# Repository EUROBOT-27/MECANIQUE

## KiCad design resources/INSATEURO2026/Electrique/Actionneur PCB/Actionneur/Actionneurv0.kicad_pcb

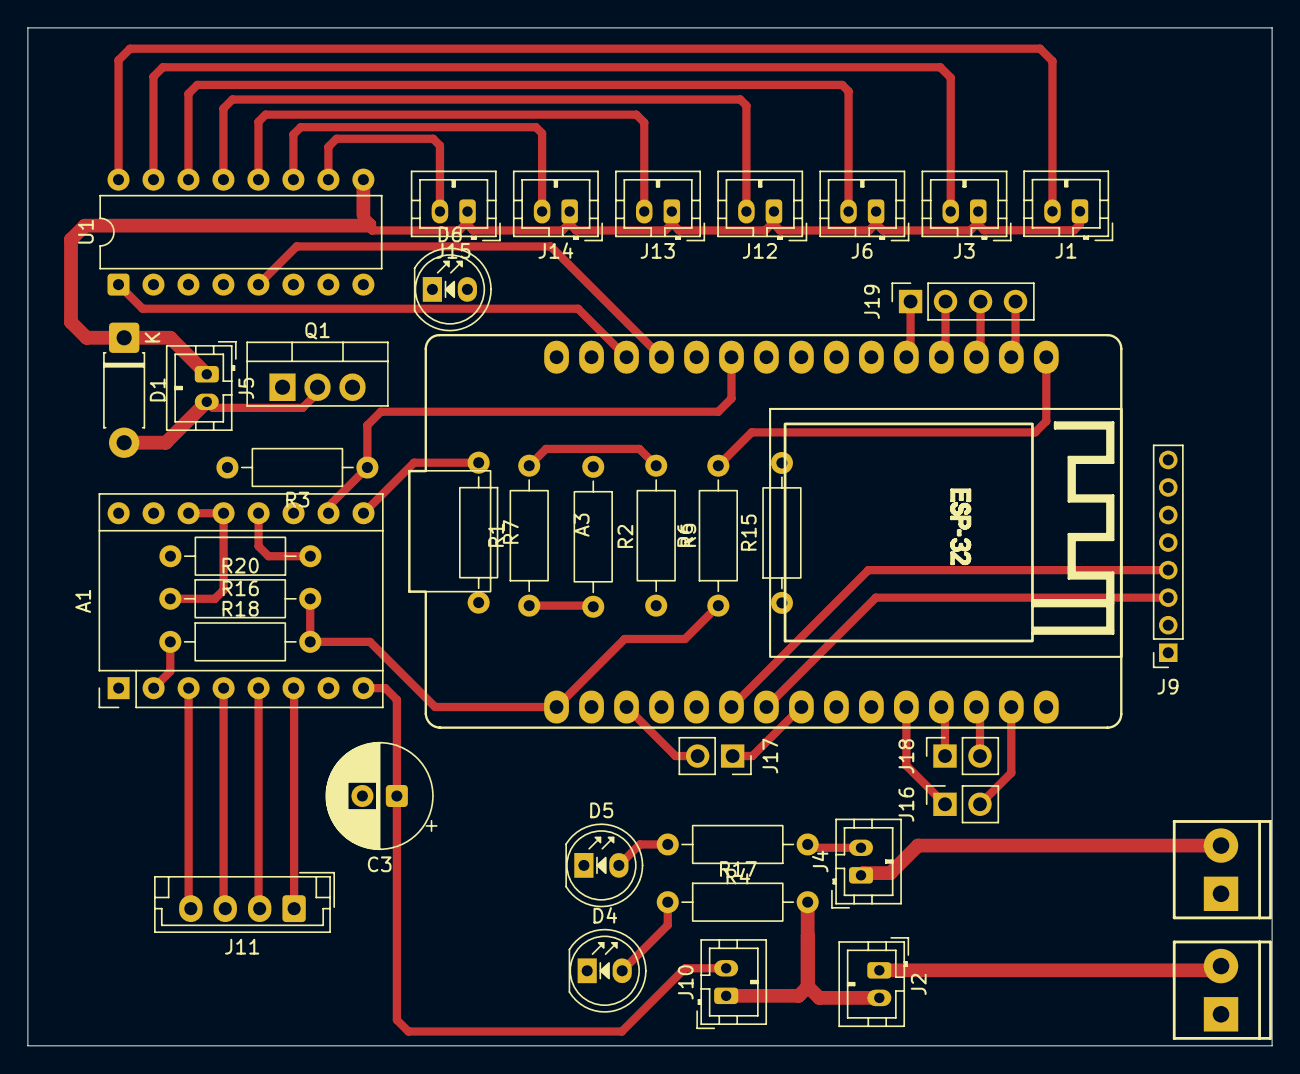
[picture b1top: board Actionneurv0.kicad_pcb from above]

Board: 2 copper layers, 90.3 x 73.9 mm, 40 parts (0 on the bottom side), 52 nets.

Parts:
A1: Pololu_Breakout_DRV8825; Pololu_Breakout-16_15.2x20.3mm
A3: ESP32_DevKit_V1_DOIT_30GPIOs; DOIT_ESP32_DEVKIT_30Pins
C3: 220u; CP_Radial_D7.5mm_P2.50mm
D1: 1N4001; D_DO-41_SOD81_P7.62mm_Horizontal
D4, D5, D6: LED; LED_D5.0mm
J1: V1; JST_PH_B2B-PH-K_1x02_P2.00mm_Vertical
J2: 12V Switch; JST_PH_B2B-PH-K_1x02_P2.00mm_Vertical
J3: V2; JST_PH_B2B-PH-K_1x02_P2.00mm_Vertical
J4: 5V Switch; JST_PH_B2B-PH-K_1x02_P2.00mm_Vertical
J5: Pump Output; JST_PH_B2B-PH-K_1x02_P2.00mm_Vertical
J6: V3; JST_PH_B2B-PH-K_1x02_P2.00mm_Vertical
J7: 12V input; ScrewTerminal_1x02_P3.5mm_Blue
J8: 5V input; ScrewTerminal_1x02_P3.5mm_Blue
J9: Maestro; PinSocket_1x08_P2.00mm_Vertical
J10: Stepper Switch; JST_PH_B2B-PH-K_1x02_P2.00mm_Vertical
J11: Stepper connector; JST_EH_B4B-EH-A_1x04_P2.50mm_Vertical
J12: V4; JST_PH_B2B-PH-K_1x02_P2.00mm_Vertical
J13: V5; JST_PH_B2B-PH-K_1x02_P2.00mm_Vertical
J14: V6; JST_PH_B2B-PH-K_1x02_P2.00mm_Vertical
J15: V7; JST_PH_B2B-PH-K_1x02_P2.00mm_Vertical
J16, J17, J18: V6; PinSocket_1x02_P2.54mm_Vertical
J19: PinSocket_1x04_P2.54mm_Vertical
Q1: IRF530N; TO-220-3_Vertical
R1: 220; R_Axial_DIN0207_L6.3mm_D2.5mm_P10.16mm_Horizontal
R2: 100k; R_Axial_DIN0207_L6.3mm_D2.5mm_P10.16mm_Horizontal
R3, R6, R7, R15, R16, R18, R20: 10k; R_Axial_DIN0207_L6.3mm_D2.5mm_P10.16mm_Horizontal
R4, R5, R17: R; R_Axial_DIN0207_L6.3mm_D2.5mm_P10.16mm_Horizontal
U1: ULN2003A; DIP-16_W7.62mm

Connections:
12V: D1.1 (K), J1.1, J2.2, J3.1, J5.1, J6.1, J10.1, J12.1, J13.1, J14.1, J15.1, R17.2, U1.9 (COM)
+3.3V: A3.1 (3.3V), R6.1, R18.2, R20.2
+5V: A3.30 (VIN), J4.2, J9.2, R4.1
D5: A3.8 (D5), J17.1
D15: A3.3 (D15/ADC2_CH3), J17.2
D34: A3.19 (ADC1_CH6/D34), J19.2
D35: A3.20 (ADC1_CH7/D35), J19.1
DIR: A1.16 (DIR), A3.10 (D19)
EV1: J1.2, U1.16 (O1)
EV2: J3.2, U1.15 (O2)
EV3: J6.2, U1.14 (O3)
EV4: J12.2, U1.13 (O4)
EV5: J13.2, U1.12 (O5)
EV6: J14.2, U1.11 (O6)
EV7: J15.2, U1.10 (O7)
GND: A1.1 (GND), A1.7 (GND), A3.2 (GND), A3.29 (GND), C3.2, D4.1 (K), D5.1 (K), D6.1 (K), J7.1, J8.1, J9.1, Q1.3 (S), R2.1, R3.2, R7.2, R15.2, R16.2, U1.8 (GND)
M0: A1.10 (M0), A3.25 (ADC2_CH7/D27), R3.1
M1: A1.11 (M1), A3.24 (DAC2/ADC2_CH9/D26), R15.1
M2: A1.12 (M2), A3.23 (DAC1/ADC2_CH8/D25), R16.1
unnamed: A1.4 (A1), J11.3
unnamed: A1.3 (A2), J11.4
unnamed: A1.5 (B1), J11.2
unnamed: A1.6 (B2), J11.1
unnamed: A1.8 (VMOT), C3.1, J10.2
unnamed: A1.9 (~EN), R7.1
unnamed: A1.2 (~FLT), R18.1
unnamed: A1.13 (~RST), A1.14 (~SLP), R20.1
unnamed: A3.16 (EN), R6.2
unnamed: D1.2 (A), J5.2, Q1.2 (D)
unnamed: D4.2 (A), R17.1
unnamed: D5.2 (A), R4.2
unnamed: D6.2 (A), R5.2
unnamed: J2.1, J7.2
unnamed: J4.1, J8.2
unnamed: Q1.1 (G), R1.1, R2.2
PUMP Signal: A3.15 (D23), R1.2, R5.1
RX: A3.6 (RX2/GPIO16), J9.4
RX0: A3.12 (RX0/GPIO3), J18.1
SCL: A3.14 (D22/SCL), J16.2
SDA: A3.11 (D21/SDA), J16.1
STEP: A1.15 (STEP), A3.9 (D18)
TX: A3.7 (TX2/GPIO17), J9.3
TX0: A3.13 (TX0/GPIO1), J18.2
VN: A3.18 (ADC1_CH3/VN), J19.3
VP: A3.17 (ADC1_CH0/VP), J19.4
Valve1: A3.28 (ADC2_CH4/D13), U1.1 (I1)
Valve2: A3.26 (ADC2_CH6/D14), U1.2 (I2)
Valve3: A3.22 (ADC1_CH4/D33), U1.3 (I3)
Valve4: A3.21 (ADC1_CH4/D32), U1.4 (I4)
Valve5: A3.27 (ADC2_CH5/D12), U1.5 (I5)
Valve6: A3.5 (D4/ADC2_CH0), U1.6 (I6)
Valve7: A3.4 (D2/ADC2_CH2), U1.7 (I7)

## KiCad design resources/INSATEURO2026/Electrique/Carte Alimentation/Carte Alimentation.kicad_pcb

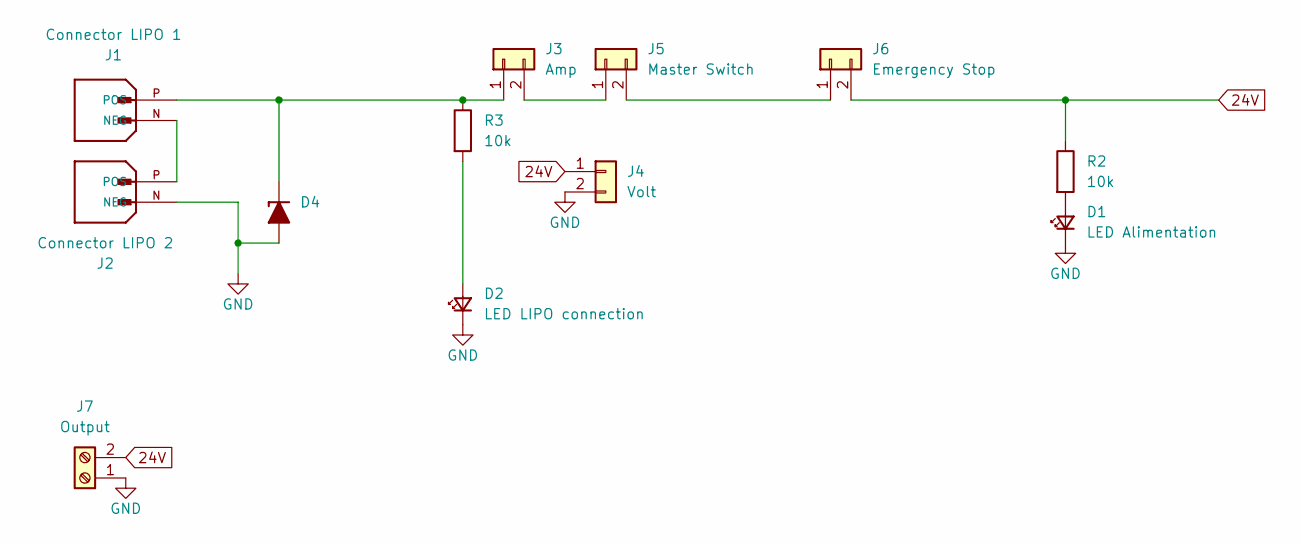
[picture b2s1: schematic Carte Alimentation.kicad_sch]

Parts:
D1: LED Alimentation; LED_D3.0mm
D2: LED LIPO connection; LED_D3.0mm
D4: P6KE24A; D_DO-15_P10.16mm_Horizontal_Zener
J1: Connector LIPO 1; AMASS_XT60-M; PARTREV V1.2
J2: Connector LIPO 2; AMASS_XT60-M; PARTREV V1.2
J3: Amp; JST_PH_B2B-PH-K_1x02_P2.00mm_Vertical
J4: Volt; JST_PH_B2B-PH-K_1x02_P2.00mm_Vertical; Part Number 1-0201FBV0T
J5: Master Switch; JST_PH_B2B-PH-K_1x02_P2.00mm_Vertical; Part Number 1-0201FBV0T
J6: Emergency Stop; JST_PH_B2B-PH-K_1x02_P2.00mm_Vertical; Part Number 1-0201FBV0T
J7: Output; TerminalBlock_Altech_AK300-2_P5.00mm
R2, R3: 10k; R_Axial_DIN0207_L6.3mm_D2.5mm_P10.16mm_Horizontal

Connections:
24V: J4.1, J6.2, J7.2, R2.1
GND: D1.1 (K), D2.1 (K), D4.2 (A), J2.N (NEG), J4.2, J7.1
unnamed: D1.2 (A), R2.2
unnamed: D2.2 (A), R3.2
unnamed: D4.1 (K), J1.P (POS), J3.1, R3.1
unnamed: J1.N (NEG), J2.P (POS)
unnamed: J3.2, J5.1
unnamed: J5.2, J6.1

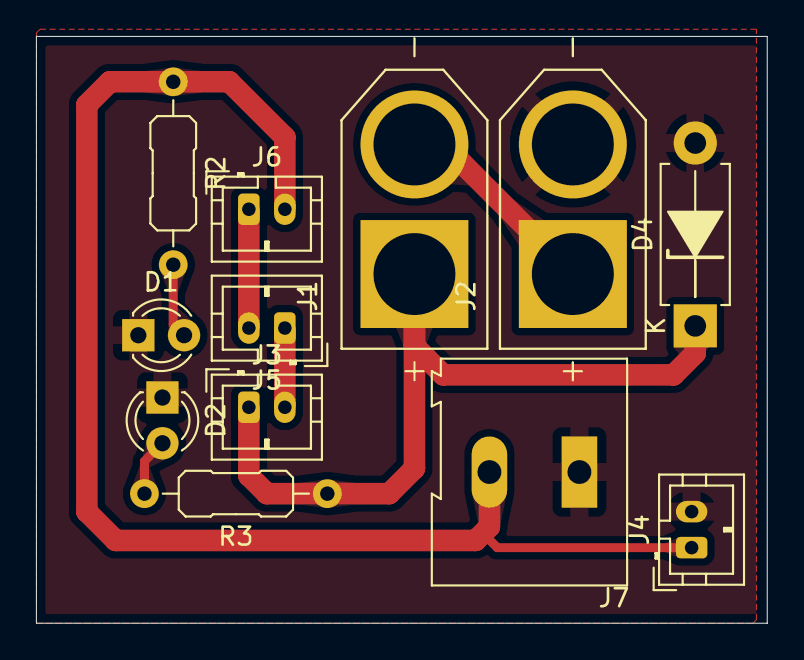
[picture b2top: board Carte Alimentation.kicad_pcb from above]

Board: 2 copper layers, 40.6 x 32.6 mm, 12 parts (0 on the bottom side), 8 nets.

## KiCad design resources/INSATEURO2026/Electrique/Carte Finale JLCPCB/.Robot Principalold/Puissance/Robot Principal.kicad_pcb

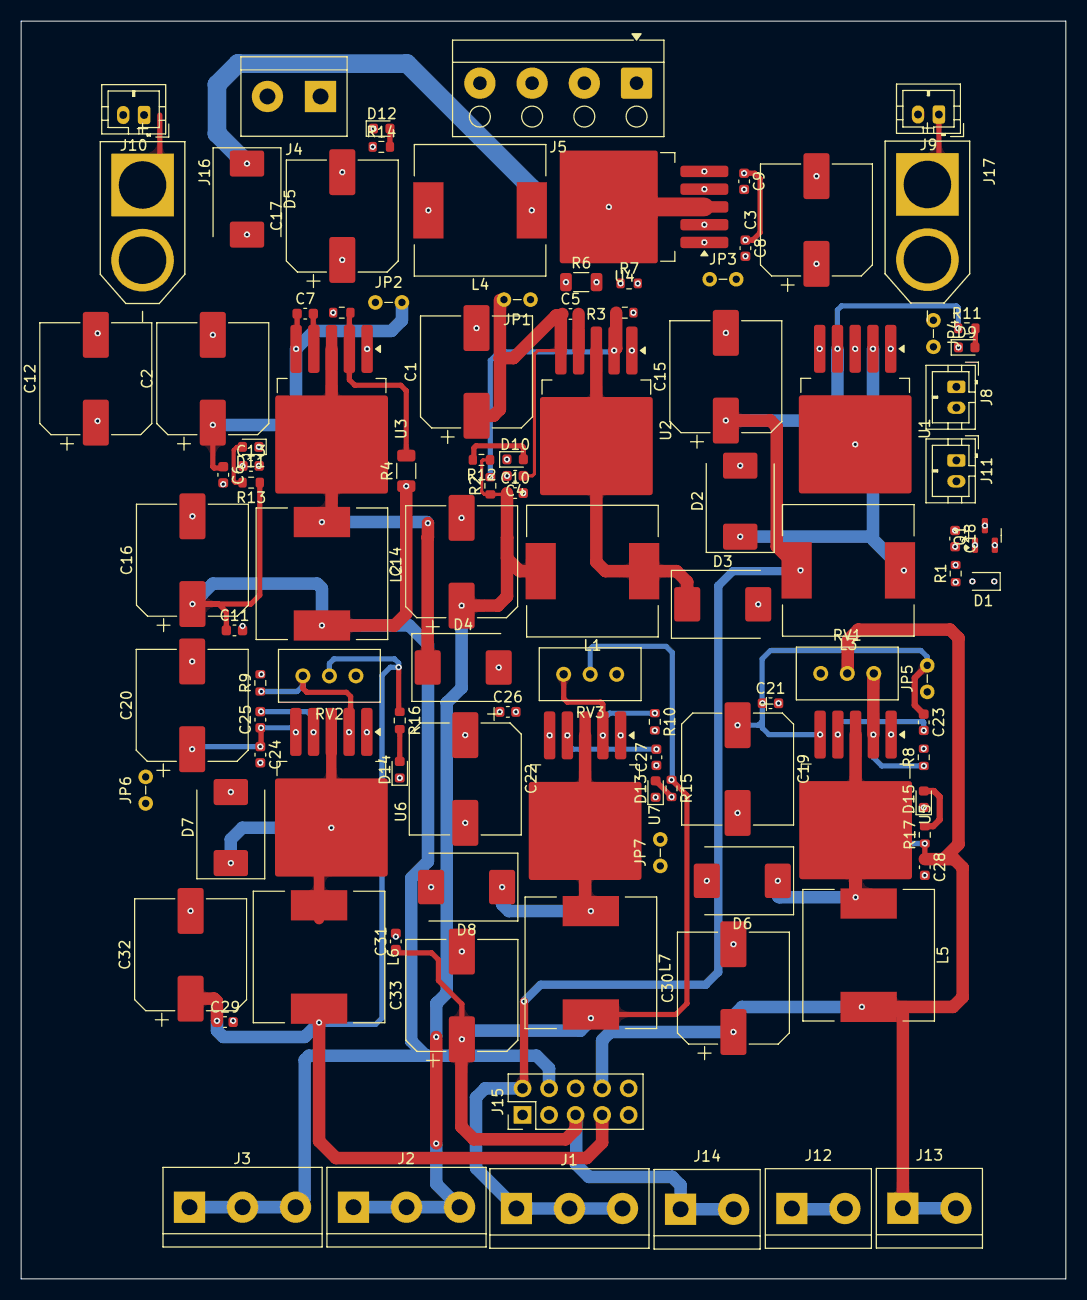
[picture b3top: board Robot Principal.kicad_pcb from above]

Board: 4 copper layers, 100.0 x 120.4 mm, 105 parts (0 on the bottom side), 47 nets.

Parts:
C1, C2, C3, C19, C20, C22: 220u; CP_Elec_10x10.5
C4, C5, C6, C7, C8, C9, C10, C11, C13, C21, C23, C24, C25, C26, C27, C28, C29, C31: 105; C_0603_1608Metric
C12: 1000u; CP_Elec_10x10.5
C14, C16, C17, C30, C32, C33: 330u; CP_Elec_10x10.5
C15: 560u; CP_Elec_10x10.5
C18: 100n; C_0603_1608Metric
D1: BZV55B10; D_SOD-323
D2: 1N5822; D_SMC
D3, D4, D5, D6, D7, D8: B540C; D_SMC
D9, D10, D11, D12, D13, D14, D15: LED; LED_0603_1608Metric
J1: 3.3v; TerminalBlock_bornier-3_P5.08mm
J2: 5V; TerminalBlock_bornier-3_P5.08mm
J3: 12V; TerminalBlock_bornier-3_P5.08mm
J4: 24V Out; TerminalBlock_bornier-2_P5.08mm
J5: Screw_Terminal_01x04; Altech_AK100_1x04_P5.00mm
J8: Emergency Stop; JST_PH_B2B-PH-K_1x02_P2.00mm_Vertical
J9: LIPO 1 VOLT; JST_PH_B2B-PH-K_1x02_P2.00mm_Vertical
J10: LIPO 2 VOLT; JST_PH_B2B-PH-K_1x02_P2.00mm_Vertical
J11: Master Switch; JST_PH_B2B-PH-K_1x02_P2.00mm_Vertical
J12, J13, J14: ADJ out; TerminalBlock_bornier-2_P5.08mm
J15: Conn_02x05_Top_Bottom; PinHeader_2x05_P2.54mm_Vertical
J16, J17: XT60-M; AMASS_XT60-M
JP1, JP2, JP3, JP4, JP5, JP6, JP7: Jumper_2_Small_Bridged; Jumper_P2.54mm_D0.7mm
L1, L2, L4, L5, L6, L7: 47uH; L_12x12mm_H6mm
L3: 33uH; L_12x12mm_H6mm
Q1: AO3401A; SOT-23
R1, R2: 10K; R_0603_1608Metric
R3, R7, R8, R9, R10: 3.3K; R_0603_1608Metric
R4: 13K; R_1206_3216Metric
R5: 1.5K; R_0603_1608Metric
R6: 60.4K; R_1206_3216Metric
R11, R12, R13, R14, R15, R16, R17: 1K; R_0603_1608Metric
RV1, RV2, RV3: R_Potentiometer; Potentiometer_Bourns_3296W_Vertical
U1: LM2596T-3.3; TO-263-5_TabPin3
U2, U3, U4, U5, U6, U7: XL4015; TO-263-5_TabPin3

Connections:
5V: C10.1, C14.1, J2.1, J2.2, J2.3, J15.3, L1.2, R2.1, R12.1
12V: C11.1, C16.1, J3.1, J3.2, J3.3, J15.4, L2.2, R4.1, R13.1
24V: C13.1, C17.1, J4.1, J4.2, L4.2, R6.1, R14.1
+3.3V: C15.1, J1.1, J1.2, J1.3, J15.2, L3.2, R11.1, U1.4 (FB)
ADJ1: C29.1, C32.1, J12.1, J12.2, J15.7, L6.2, R16.1, RV2.2
ADJ2: C28.1, C30.1, J13.1, J13.2, J15.8, L5.2, R17.1, RV1.2
GND: C1.2, C2.2, C3.2, C4.2, C6.2, C8.2, C10.2, C11.2, C12.2, C13.2, C14.2, C15.2, C16.2, C17.2, C18.2, C19.2, C20.2, C21.2, C22.2, C24.2, C26.2, C28.2, C29.2, C30.2, C31.2, C32.2, C33.2, D2.2 (A), D3.2 (A), D4.2 (A), D5.2 (A), D6.2 (A), D7.2 (A), D8.2 (A), D9.1 (K), D10.1 (K), D11.1 (K), D12.1 (K), D13.1 (K), D14.1 (K), D15.1 (K), J5.1, J5.2, J5.3, J5.4, J9.2, J10.2, J15.1, J15.6, J16.N (NEG), R1.2, R3.2, R5.2, R7.2, R8.2, R9.2, R10.2, RV1.3, RV2.3, RV3.3, U1.3 (GND), U1.5 (~ON/OFF), U2.1 (GND), U3.1 (GND), U4.1 (GND), U5.1 (GND), U6.1 (GND), U7.1 (GND)
unnamed: D1.2 (A), Q1.1 (G), R1.1
unnamed: D2.1 (K), L3.1, U1.2 (OUT)
unnamed: D3.1 (K), L1.1, U2.3 (SW)
unnamed: D4.1 (K), L2.1, U3.3 (SW)
unnamed: D5.1 (K), L4.1, U4.3 (SW)
unnamed: D6.1 (K), L5.1, U5.3 (SW)
unnamed: D7.1 (K), L6.1, U6.3 (SW)
unnamed: D8.1 (K), L7.1, U7.3 (SW)
unnamed: D9.2 (A), R11.2
unnamed: D10.2 (A), R12.2
unnamed: D11.2 (A), R13.2
unnamed: D12.2 (A), R14.2
unnamed: D13.2 (A), R15.2
unnamed: D14.2 (A), R16.2
unnamed: D15.2 (A), R17.2
unnamed: J10.1, J16.P (POS), J17.N (NEG)
unnamed: J8.2, J11.1
unnamed: J8.1, J9.1, J17.P (POS)
unnamed: C1.1, C4.1, C5.1, JP1.2 (B), U2.5 (VIN)
unnamed: C2.1, C6.1, C7.1, JP2.2 (B), U3.5 (VIN)
unnamed: C3.1, C8.1, C9.1, JP3.2 (B), U4.5 (VIN)
unnamed: JP4.2 (B), U1.1 (VIN)
unnamed: C19.1, C21.1, C23.1, JP5.2 (B), U5.5 (VIN)
unnamed: C20.1, C24.1, C25.1, JP6.2 (B), U6.5 (VIN)
unnamed: C22.1, C26.1, C27.1, JP7.2 (B), U7.5 (VIN)
unnamed: R2.2, R3.1, U2.2 (FB)
unnamed: C5.2, U2.4 (VC)
unnamed: R4.2, R5.1, U3.2 (FB)
unnamed: C7.2, U3.4 (VC)
unnamed: R6.2, R7.1, U4.2 (FB)
unnamed: C9.2, U4.4 (VC)
unnamed: R8.1, RV1.1, U5.2 (FB)
unnamed: C23.2, U5.4 (VC)
unnamed: R9.1, RV2.1, U6.2 (FB)
unnamed: C25.2, U6.4 (VC)
unnamed: R10.1, RV3.1, U7.2 (FB)
unnamed: C27.2, U7.4 (VC)
SERVO: C31.1, C33.1, J14.1, J14.2, J15.5, L7.2, R15.1, RV3.2
SUPPLY: J11.2, Q1.3 (D)
VDC: C12.1, C18.1, D1.1 (K), JP1.1 (A), JP2.1 (A), JP3.1 (A), JP4.1 (A), JP5.1 (A), JP6.1 (A), JP7.1 (A), Q1.2 (S)

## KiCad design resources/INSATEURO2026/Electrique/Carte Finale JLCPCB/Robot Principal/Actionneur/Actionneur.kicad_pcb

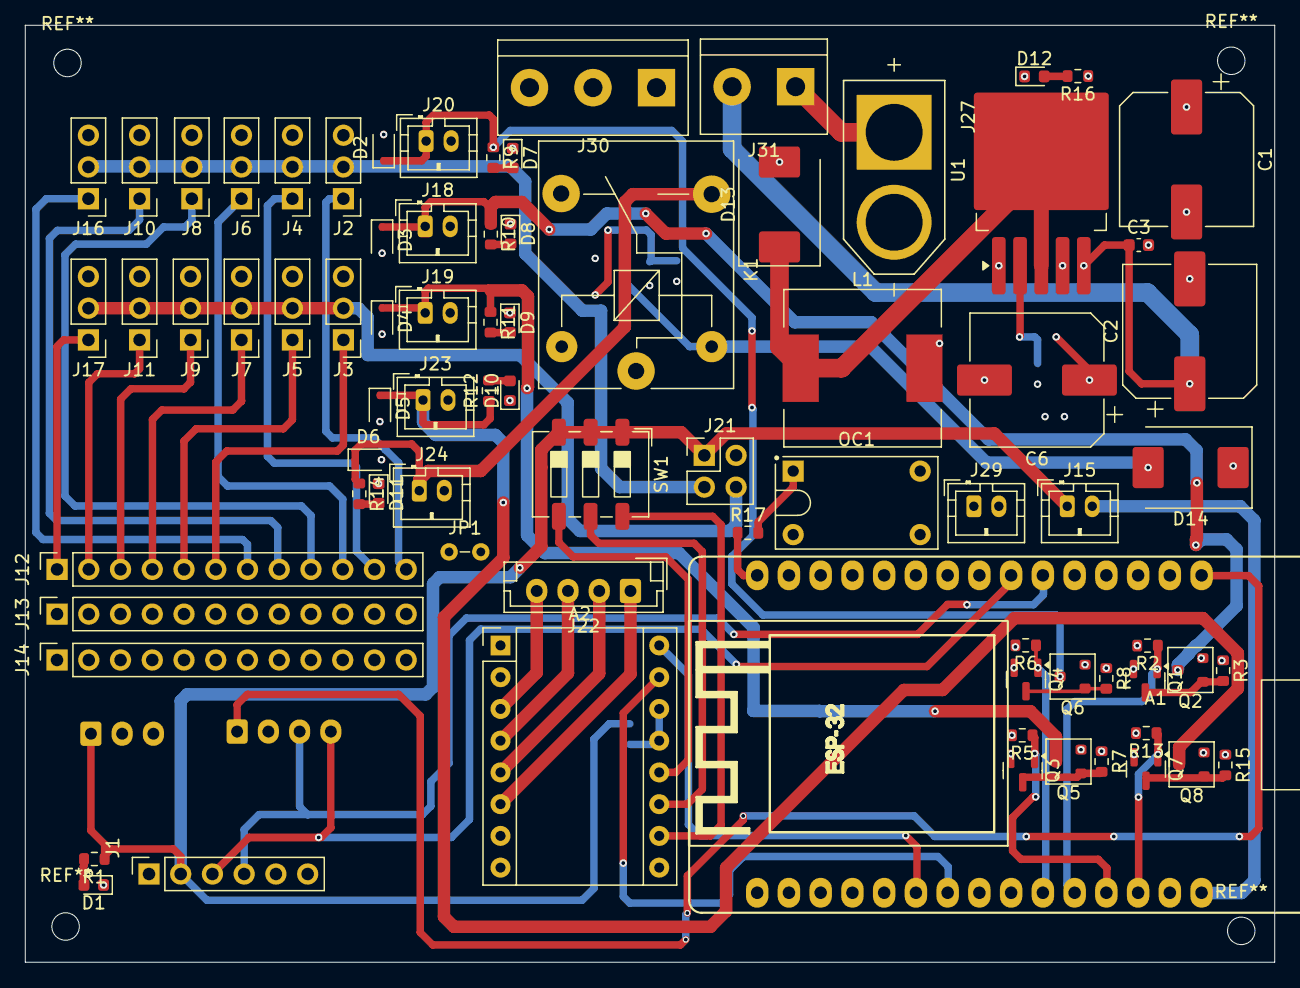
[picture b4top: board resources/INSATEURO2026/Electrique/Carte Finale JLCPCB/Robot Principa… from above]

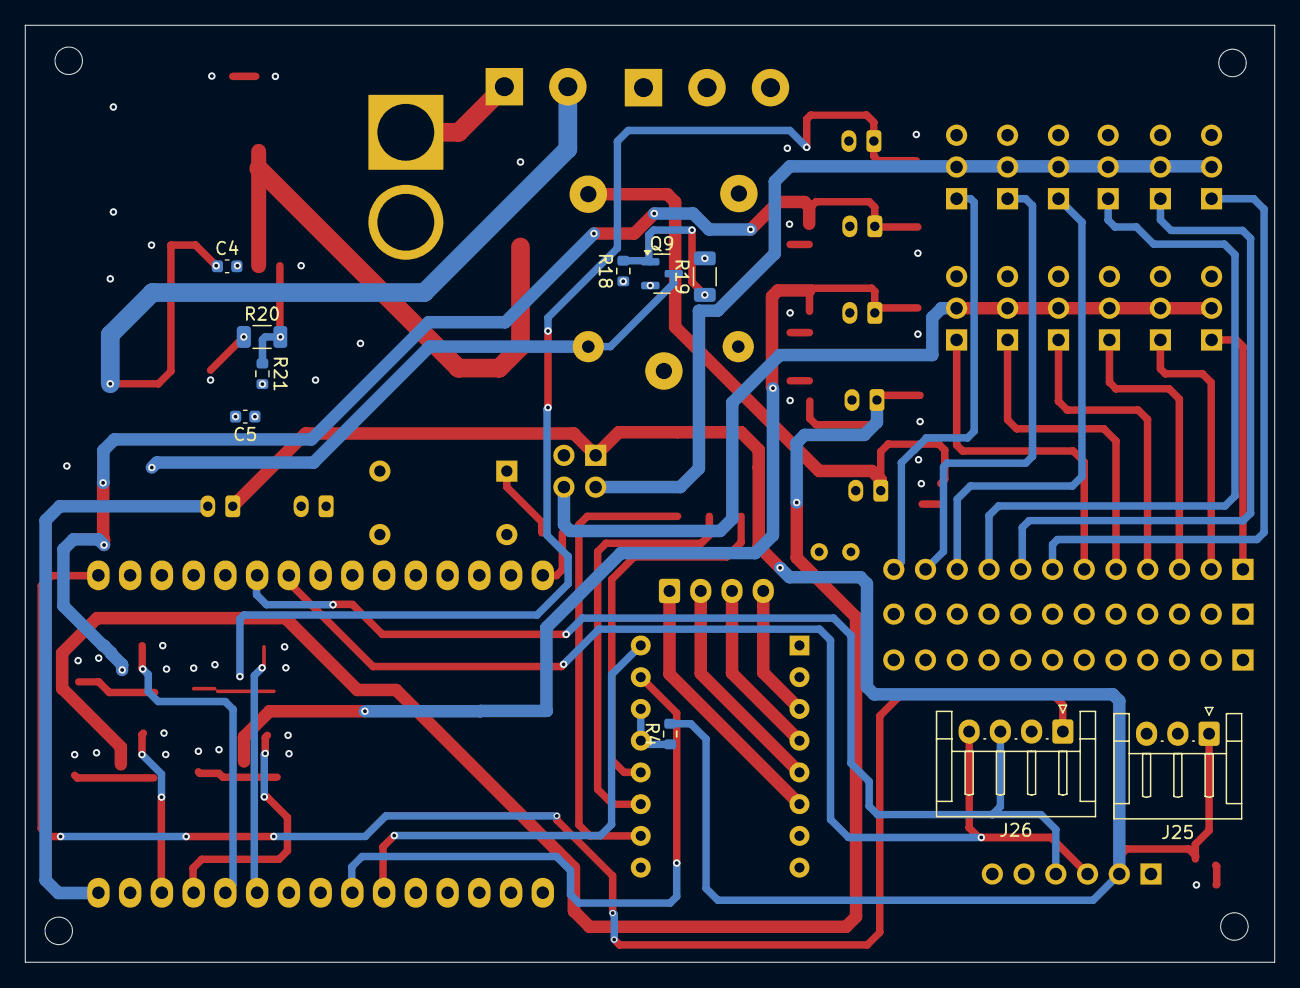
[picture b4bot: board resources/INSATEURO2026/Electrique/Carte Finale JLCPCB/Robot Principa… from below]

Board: 4 copper layers, 100.0 x 75.0 mm, 88 parts (10 on the bottom side), 61 nets.

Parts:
A1: ESP32_DevKit_V1_DOIT_30GPIOs; DOIT_ESP32_DEVKIT_30Pins
A2: Pololu_Breakout_DRV8825; Pololu_Breakout-16_15.2x20.3mm
C1, C2: 220u; CP_Elec_10x10.5
C3, C4, C5: 105; C_0603_1608Metric
C6: 330u; CP_Elec_10x10.5
D1, D7, D8, D9, D10, D11, D12: LED; LED_0603_1608Metric
D2, D3, D4, D5, D6: SS34; D_SOD-323
D13: B540C; D_SMC
D14: 1N5819M; D_SMC
J1: Conn_01x06; PinSocket_1x06_P2.54mm_Vertical
J2: Servo 7; PinHeader_1x03_P2.54mm_Vertical
J3: Servo 1; PinHeader_1x03_P2.54mm_Vertical
J4: Servo 8; PinHeader_1x03_P2.54mm_Vertical
J5: Servo 2; PinHeader_1x03_P2.54mm_Vertical
J6: Servo 9; PinHeader_1x03_P2.54mm_Vertical
J7: Servo 3; PinHeader_1x03_P2.54mm_Vertical
J8: Servo 10; PinHeader_1x03_P2.54mm_Vertical
J9: Servo 4; PinHeader_1x03_P2.54mm_Vertical
J10: Servo 11; PinHeader_1x03_P2.54mm_Vertical
J11: Servo 5; PinHeader_1x03_P2.54mm_Vertical
J12: PWM; PinSocket_1x12_P2.54mm_Vertical
J13: VCC; PinSocket_1x12_P2.54mm_Vertical
J14: GND; PinSocket_1x12_P2.54mm_Vertical
J15, J18, J19, J20, J23, J24: V1; JST_PH_B2B-PH-K_1x02_P2.00mm_Vertical
J16: Servo 12; PinHeader_1x03_P2.54mm_Vertical
J17: Servo 6; PinHeader_1x03_P2.54mm_Vertical
J21: Conn_02x05_Top_Bottom; PinHeader_2x02_P2.54mm_Vertical
J22: Stepper connector; JST_EH_B4B-EH-A_1x04_P2.50mm_Vertical
J25: Conn_01x03; JST_EH_S3B-EH_1x03_P2.50mm_Horizontal
J26: Conn_01x04; JST_EH_S4B-EH_1x04_P2.50mm_Horizontal
J27: XT60-M; AMASS_XT60-M
J29: Pump Lipo Voltage; JST_PH_B2B-PH-K_1x02_P2.00mm_Vertical
J30: 12V; TerminalBlock_bornier-3_P5.08mm
J31: ADJ out; TerminalBlock_bornier-2_P5.08mm
JP1: Jumper_2_Bridged; Jumper_P2.54mm_D0.7mm
K1: SANYOU_SRD_Form_C; Relay_SPDT_SANYOU_SRD_Series_Form_C
L1: 47uH; L_12x12mm_H6mm
OC1: PC817; Vishay_CNY64
Q1, Q3, Q4, Q7, Q9: AO3400A; SOT-23
Q2, Q5, Q6, Q8: AO3401A; SOT-23
R1: 330; R_0603_1608Metric
R2, R3, R5, R6, R7, R8, R13, R15: 100K; R_0603_1608Metric
R4: 10k; R_0603_1608Metric
R9, R10, R11, R12, R14, R16: 1K; R_0603_1608Metric
R17: 470; R_0603_1608Metric
R18: 270; R_0603_1608Metric
R19: 100k; R_1206_3216Metric
R20: 13K; R_1206_3216Metric
R21: 1.5K; R_0603_1608Metric
SW1: SW_DIP_x03; SW_DIP_SPSTx03_Slide_6.7x9.18mm_W6.73mm_P2.54mm_LowProfile_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
U1: XL4015; TO-263-5_TabPin3

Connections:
12V: A2.8 (VMOT), C1.1, C5.1, C6.1, D14.1 (K), J30.1, J30.2, J30.3, K1.1, K1.5, L1.2, OC1.4, Q2.2 (S), Q5.2 (S), Q6.2 (S), Q8.2 (S), R3.1, R7.1, R8.1, R15.1, R16.1, R20.1
+3.3V: A1.1 (3.3V), J26.1
+5V: J1.2, J15.1, J21.1, J25.1, R1.1, R4.2, SW1.1, SW1.2, SW1.3
ADJ1: J3.2, J5.2, J7.2, J9.2, J11.2, J17.2, J21.4
DIR: A1.21 (ADC1_CH4/D32), A2.16 (DIR)
EV1: D2.1 (K), J20.1, Q6.3 (D), R9.1
EV2: D3.1 (K), J18.1, Q2.3 (D), R10.1
EV3: D4.1 (K), J19.1, Q5.3 (D), R11.1
EV4: D5.1 (K), J23.1, Q8.3 (D), R12.1
GND: A1.2 (GND), A1.29 (GND), A2.1 (GND), A2.7 (GND), C1.2, C2.2, C3.2, C5.2, C6.2, D1.1 (K), D7.1 (K), D8.1 (K), D9.1 (K), D10.1 (K), D11.1 (K), D12.1 (K), D13.2 (A), J1.1, J21.2, J25.2, J26.2, JP1.2 (B), OC1.2, R21.2, U1.1 (GND)
GNDPWR: D2.2 (A), D3.2 (A), D4.2 (A), D5.2 (A), D6.2 (A), J2.3, J3.3, J4.3, J5.3, J6.3, J7.3, J8.3, J9.3, J10.3, J11.3, J14.1, J14.2, J14.3, J14.4, J14.5, J14.6, J14.7, J14.8, J14.9, J14.10, J14.11, J14.12, J16.3, J17.3, J18.2, J19.2, J20.2, J23.2, J24.2, J27.N (NEG), J29.2, JP1.1 (A), OC1.3, Q1.2 (S), Q3.2 (S), Q4.2 (S), Q7.2 (S), Q9.2 (S), R2.2, R5.2, R6.2, R13.2, R18.1, R19.2
unnamed: A1.30 (VIN), J15.2
unnamed: A2.4 (A1), J22.3
unnamed: A2.3 (A2), J22.4
unnamed: A2.5 (B1), J22.2
unnamed: A2.6 (B2), J22.1
unnamed: A2.10 (M0), SW1.6
unnamed: A2.11 (M1), SW1.5
unnamed: A2.12 (M2), SW1.4
unnamed: A2.13 (~RST), A2.14 (~SLP), R4.1
unnamed: D1.2 (A), R1.2
unnamed: D7.2 (A), R9.2
unnamed: D8.2 (A), R10.2
unnamed: D9.2 (A), R11.2
unnamed: D10.2 (A), R12.2
unnamed: D11.2 (A), R14.2
unnamed: D12.2 (A), R16.2
unnamed: D13.1 (K), L1.1, U1.3 (SW)
unnamed: D14.2 (A), K1.2, Q9.3 (D)
unnamed: J27.P (POS), J29.1, J31.1
unnamed: OC1.1, R17.2
unnamed: Q1.3 (D), Q2.1 (G), R3.2
unnamed: Q3.3 (D), Q5.1 (G), R7.2
unnamed: Q4.3 (D), Q6.1 (G), R8.2
unnamed: Q7.3 (D), Q8.1 (G), R15.2
unnamed: Q9.1 (G), R18.2, R19.1
unnamed: R20.2, R21.1, U1.2 (FB)
unnamed: C4.2, U1.4 (VC)
PWM1: J12.1, J17.1
PWM2: J11.1, J12.2
PWM3: J9.1, J12.3
PWM4: J7.1, J12.4
PWM5: J5.1, J12.5
PWM6: J3.1, J12.6
PWM7: J12.7, J16.1
PWM8: J10.1, J12.8
PWM9: J8.1, J12.9
PWM10: J6.1, J12.10
PWM11: J4.1, J12.11
PWM12: J2.1, J12.12
Pump: D6.1 (K), J24.1, K1.3, R14.1
Pump Signal: A1.15 (D23), R17.1
RX: A1.6 (RX2/GPIO16), J1.4, J26.3
SERVO: J2.2, J4.2, J6.2, J8.2, J10.2, J16.2, J21.3
STEP: A1.22 (ADC1_CH4/D33), A2.15 (STEP)
TX: A1.7 (TX2/GPIO17), J1.3, J26.4
VDC: C2.1, C3.1, C4.1, J31.2, U1.5 (VIN)
Valve 1 Signal: A1.25 (ADC2_CH7/D27), Q4.1 (G), R6.1
Valve 2 Signal: A1.26 (ADC2_CH6/D14), Q1.1 (G), R2.1
Valve 3 Signal: A1.27 (ADC2_CH5/D12), Q3.1 (G), R5.1
Valve 4 Signal: A1.28 (ADC2_CH4/D13), Q7.1 (G), R13.1

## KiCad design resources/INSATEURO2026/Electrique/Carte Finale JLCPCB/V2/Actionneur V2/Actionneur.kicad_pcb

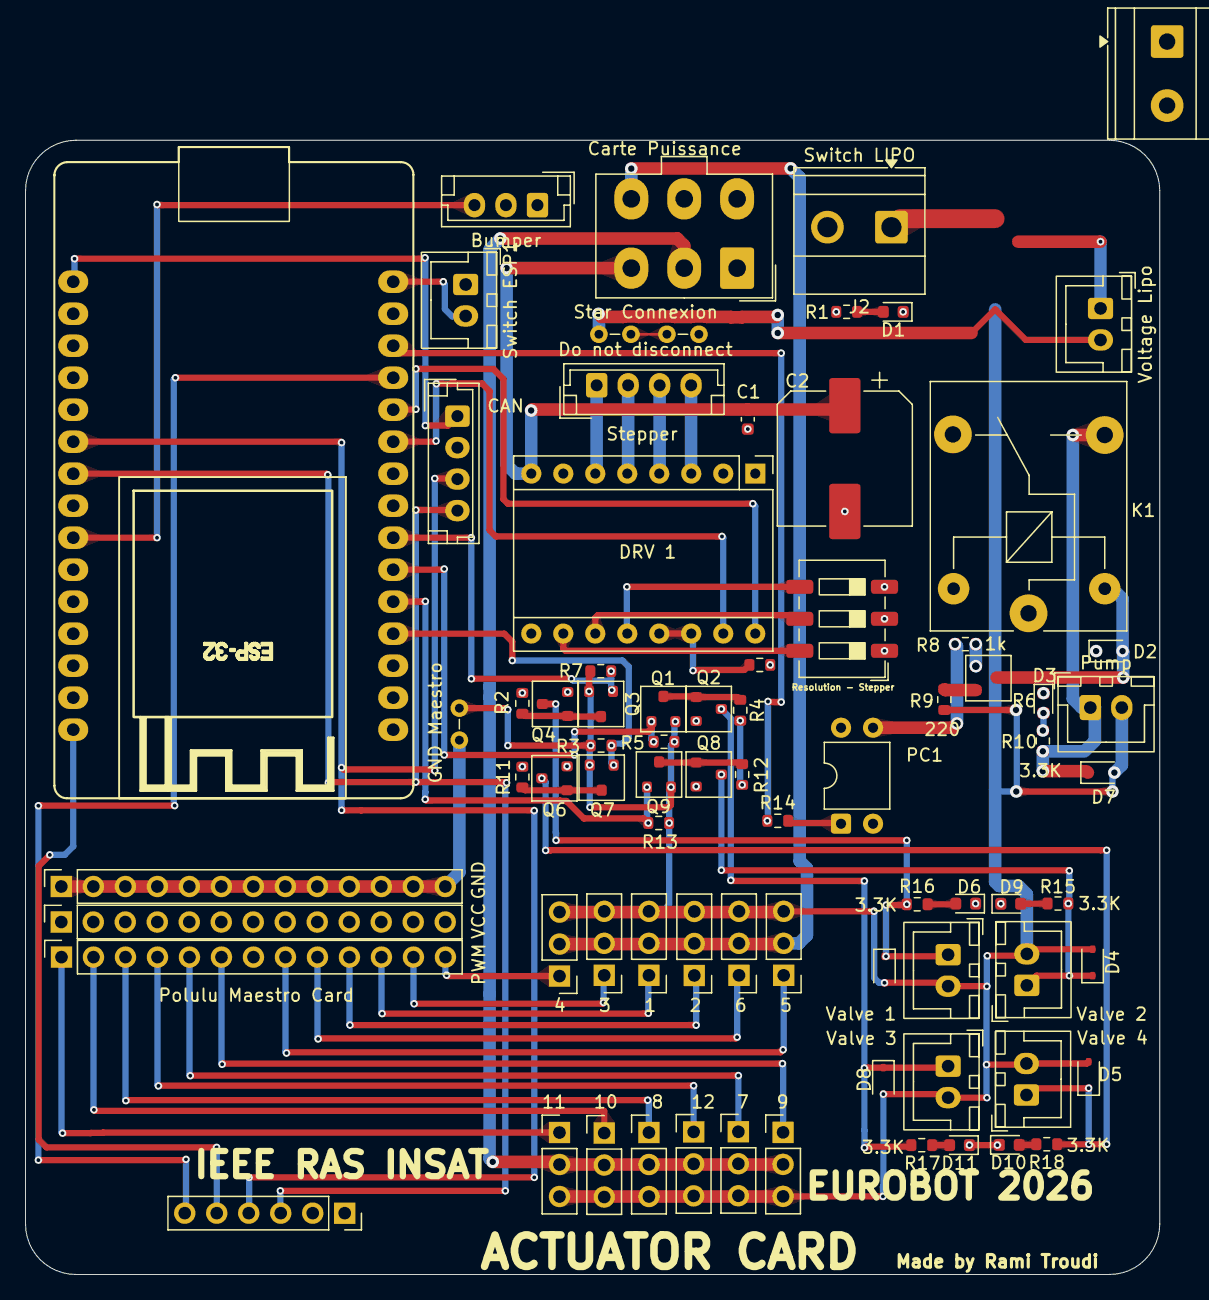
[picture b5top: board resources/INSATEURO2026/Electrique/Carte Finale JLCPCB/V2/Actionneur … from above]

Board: 4 copper layers, 90.0 x 90.0 mm, 78 parts (0 on the bottom side), 64 nets.

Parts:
1: Servo 9; PinHeader_1x03_P2.54mm_Vertical
2: Servo 12; PinHeader_1x03_P2.54mm_Vertical
3: Servo 8; PinHeader_1x03_P2.54mm_Vertical
4: Servo 11; PinHeader_1x03_P2.54mm_Vertical
5: Servo 7; PinHeader_1x03_P2.54mm_Vertical
6: Servo 10; PinHeader_1x03_P2.54mm_Vertical
7: Servo 3; PinHeader_1x03_P2.54mm_Vertical
8: Servo 6; PinHeader_1x03_P2.54mm_Vertical
9: Servo 4; PinHeader_1x03_P2.54mm_Vertical
10: Servo 5; PinHeader_1x03_P2.54mm_Vertical
11: Servo 1; PinHeader_1x03_P2.54mm_Vertical
12: Servo 2; PinHeader_1x03_P2.54mm_Vertical
A1: ESP32_DevKit_V1_DOIT_30GPIOs; DOIT_ESP32_DEVKIT_30Pins
Bumper: Conn_01x03; JST_EH_B3B-EH-A_1x03_P2.50mm_Vertical
C1: 105; C_0603_1608Metric
C2: 1000u; CP_Elec_10x10.5
CAN: Conn_01x04; JST_EH_B4B-EH-A_1x04_P2.50mm_Vertical
Carte Puissance: Conn_02x03; Molex_Mini-Fit_Jr_5566-06A_2x03_P4.20mm_Vertical
D1, D3, D6, D9, D10, D11: LED; LED_0603_1608Metric
D2, D4, D5, D7, D8: SS34; D_SOD-323
DRV 1: Pololu_Breakout_DRV8825; Pololu_Breakout-16_15.2x20.3mm
GND: GND; PinSocket_1x13_P2.54mm_Vertical
GND Maestro: Jumper_2_Open; Jumper_P2.54mm_D0.7mm
J1: XT60-M; TerminalBlock_Phoenix_MKDS-1,5-2-5.08_1x02_P5.08mm_Horizont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
J2: Switch LIPO; TerminalBlock_Phoenix_MKDS-1,5-2-5.08_1x02_P5.08mm_Horizont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
J3: Conn_01x06; PinSocket_1x06_P2.54mm_Vertical
JP1: Jumper_2_Open; Jumper_P2.54mm_D0.7mm
K1: SANYOU_SRD_Form_C; Relay_SPDT_SANYOU_SRD_Series_Form_C
PC1: PC817; DIP-4_W7.62mm
PWM: PWM; PinSocket_1x13_P2.54mm_Vertical
Polulu Maestro Card: SS34; D_SOD-323
Pump: V1; JST_XH_B2B-XH-A_1x02_P2.50mm_Vertical
Q1, Q3, Q5, Q7, Q9: BC817; SOT-23
Q2, Q4, Q6, Q8: AO3401A; SOT-23
R1, R10, R15, R16, R17, R18: 3.3K; R_0603_1608Metric
R2, R3, R4, R5, R7, R11, R12, R13: 10K; R_0603_1608Metric
R6: 10k; R_0603_1608Metric
R8: 1k; R_0603_1608Metric
R9, R14: 220; R_0603_1608Metric
Resolution - Stepper: SW_DIP_x03; SW_DIP_SPSTx03_Slide_6.7x9.18mm_W6.73mm_P2.54mm_LowProfile_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
Star Connexion: Jumper_2_Open; Jumper_P2.54mm_D0.7mm
Stepper: Stepper connector; JST_EH_B4B-EH-A_1x04_P2.50mm_Vertical
Switch ESP1: V1; JST_XH_B2B-XH-A_1x02_P2.50mm_Vertical
VCC: VCC; PinSocket_1x13_P2.54mm_Vertical
Valve 1, Valve 2, Valve 3, Valve 4: V1; JST_XH_B2B-XH-A_1x02_P2.50mm_Vertical
Voltage Lipo: Pump Lipo Voltage; JST_XH_B2B-XH-A_1x02_P2.50mm_Vertical

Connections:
12V: C1.1, C2.1, Carte Puissance.3, DRV 1.8 (VMOT)
+3.3V: A1.1 (3.3V), CAN.1
+5V: Bumper.1, Carte Puissance.1, J3.2, R6.2, Resolution - Stepper.1, Resolution - Stepper.2, Resolution - Stepper.3
DIR: A1.26 (ADC2_CH6/D14), DRV 1.16 (DIR)
ERR: A1.27 (ADC2_CH5/D12), J3.6
EV1: D5.1 (K), Q6.3 (D), R18.1, Valve 4.1
EV2: D4.1 (K), Q8.3 (D), R15.1, Valve 2.1
EV3: D8.1 (K), Q2.3 (D), R17.1, Valve 3.1
EV4: Polulu Maestro Card.1 (K), Q4.3 (D), R16.1, Valve 1.1
GND: A1.2 (GND), A1.29 (GND), Bumper.2, C1.2, C2.2, CAN.2, Carte Puissance.4, Carte Puissance.5, D1.1 (K), D3.1 (K), D6.1 (K), D9.1 (K), D10.1 (K), D11.1 (K), DRV 1.1 (GND), DRV 1.7 (GND), J3.1, PC1.2, Star Connexion.2 (B)
GNDPWR: 1.3, 2.3, 3.3, 4.3, 5.3, 6.3, 7.3, 8.3, 9.3, 10.3, 11.3, 12.3, D4.2 (A), D5.2 (A), D7.2 (A), D8.2 (A), GND Maestro.2 (B), JP1.1 (A), Polulu Maestro Card.2 (A), Pump.2, Q1.2 (E), Q3.2 (E), Q7.2 (E), Q9.2 (E), R3.2, R5.2, R7.2, R9.1, R13.2, Valve 1.2, Valve 2.2, Valve 3.2, Valve 4.2, Voltage Lipo.2
unnamed: A1.30 (VIN), Switch ESP1.2
unnamed: DRV 1.4 (A1), Stepper.3
unnamed: DRV 1.3 (A2), Stepper.4
unnamed: DRV 1.5 (B1), Stepper.2
unnamed: DRV 1.6 (B2), Stepper.1
unnamed: DRV 1.10 (M0), Resolution - Stepper.6
unnamed: DRV 1.11 (M1), Resolution - Stepper.5
unnamed: DRV 1.12 (M2), Resolution - Stepper.4
unnamed: DRV 1.13 (~RST), DRV 1.14 (~SLP), R6.1
unnamed: D2.2 (A), K1.2, Q5.3 (C)
unnamed: D10.2 (A), R18.2
unnamed: D9.2 (A), R15.2
unnamed: D11.2 (A), R17.2
unnamed: D6.2 (A), R16.2
unnamed: D3.2 (A), R10.2
unnamed: D1.2 (A), R1.2
unnamed: GND.1, GND.2, GND.3, GND.4, GND.5, GND.6, GND.7, GND.8, GND.9, GND.10, GND.11, GND.12, GND.13, GND Maestro.1 (A)
unnamed: J2.1, Voltage Lipo.1
unnamed: JP1.2 (B), Star Connexion.1 (A)
unnamed: PC1.1, R14.2
unnamed: PC1.3, R8.1
unnamed: Q8.1 (G), Q9.3 (C), R12.2
unnamed: Q1.3 (C), Q2.1 (G), R4.2
unnamed: Q6.1 (G), Q7.3 (C), R11.2
unnamed: Q3.3 (C), Q4.1 (G), R2.2
unnamed: Q5.1 (B), R8.2
unnamed: Q5.2 (E), R9.2
PWM1: 5.1, PWM.13
PWM2: 3.1, PWM.12
PWM3: 1.1, PWM.11
PWM4: 6.1, PWM.10
PWM5: 4.1, PWM.9
PWM6: 2.1, PWM.8
PWM7: 11.1, PWM.6
PWM8: 12.1, PWM.5
PWM9: 7.1, PWM.4
PWM10: 9.1, PWM.3
PWM11: 10.1, PWM.2
PWM12: 8.1, PWM.1
Pump: D7.1 (K), K1.3, Pump.1, R10.1
Pump Signal: A1.28 (ADC2_CH4/D13), R14.1
RST: A1.15 (D23), J3.5
RX: A1.6 (RX2/GPIO16), CAN.3, J3.4
SERVO PWR1: 7.2, 8.2, 9.2, 10.2, 11.2, 12.2, Carte Puissance.2
SERVO PWR2: 1.2, 2.2, 3.2, 4.2, 5.2, 6.2, Carte Puissance.6
SIG: A1.9 (D18), Bumper.3
STEP: A1.25 (ADC2_CH7/D27), DRV 1.15 (STEP)
TX: A1.7 (TX2/GPIO17), CAN.4, J3.3
VDC: D2.1 (K), J2.2, K1.1, K1.5, PC1.4, Q2.2 (S), Q4.2 (S), Q6.2 (S), Q8.2 (S), R1.1, R2.1, R4.1, R11.1, R12.1
Valve 1 Signal: A1.19 (ADC1_CH6/D34), Q7.1 (B), R3.1
Valve 2 Signal: A1.20 (ADC1_CH7/D35), Q9.1 (B), R13.1
Valve 3 Signal: A1.21 (ADC1_CH4/D32), Q1.1 (B), R5.1
Valve 4 Signal: A1.22 (ADC1_CH4/D33), Q3.1 (B), R7.1

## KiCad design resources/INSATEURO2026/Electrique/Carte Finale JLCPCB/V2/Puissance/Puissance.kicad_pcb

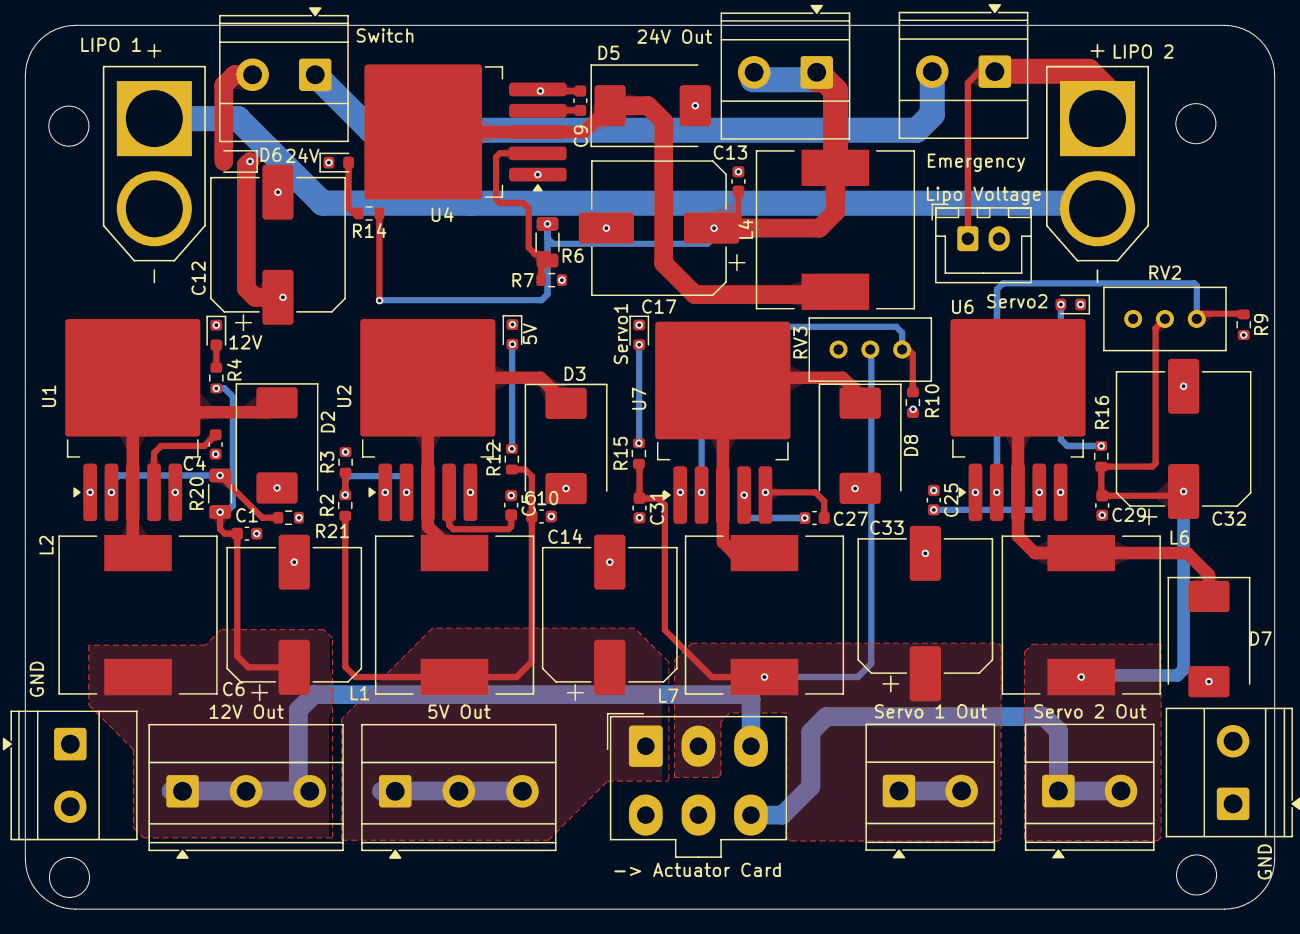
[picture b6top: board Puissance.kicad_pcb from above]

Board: 4 copper layers, 99.8 x 70.6 mm, 65 parts (0 on the bottom side), 31 nets.

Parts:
5V, 12V, 24V: LED; LED_0603_1608Metric
5V Out: 5V; TerminalBlock_Phoenix_MKDS-1,5-3-5.08_1x03_P5.08mm_Horizont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
12V Out: 12V; TerminalBlock_Phoenix_MKDS-1,5-3-5.08_1x03_P5.08mm_Horizont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
24V Out: 24V Out; TerminalBlock_Phoenix_MKDS-1,5-2_1x02_P5.00mm_Horizontal
-> Actuator Card: Conn_02x03; Molex_Mini-Fit_Jr_5566-06A_2x03_P4.20mm_Vertical
C1, C4, C5, C9, C10, C13, C25, C27, C29, C31: 105; C_0603_1608Metric
C6, C14, C17, C32, C33: 330u; CP_Elec_10x10.5
C12: 1000u; CP_Elec_10x10.5
D2, D3, D5, D7, D8: B540C; D_SMC
D6: SS34; D_SOD-323
Emergency: Emergency Stop; TerminalBlock_Phoenix_MKDS-1,5-2_1x02_P5.00mm_Horizontal
GND: ADJ out; TerminalBlock_Phoenix_MKDS-1,5-2_1x02_P5.00mm_Horizontal
GND : ADJ out; TerminalBlock_Phoenix_MKDS-1,5-2_1x02_P5.00mm_Horizontal
L1, L2, L4, L6, L7: 47uH; L_12x12mm_H6mm
LIPO 1, LIPO 2: XT60-M; AMASS_XT60-M
Lipo Voltage: LIPO 1 VOLT; JST_XH_B2B-XH-A_1x02_P2.50mm_Vertical
R2: 10K; R_0603_1608Metric
R3, R7, R9, R10: 3.3K; R_0603_1608Metric
R4: 1k; R_0603_1608Metric
R6: 60.4K; R_1206_3216Metric
R12: 220; R_0603_1608Metric
R14: 3.3k; R_0603_1608Metric
R15, R16: 1K; R_0603_1608Metric
R20: 13K; R_1206_3216Metric
R21: 1.5K; R_0603_1608Metric
RV2, RV3: R_Potentiometer; Potentiometer_Bourns_3296W_Vertical
Servo1, Servo2: LED; LED_0603_1608Metric
Servo 1 Out, Servo 2 Out: ADJ out; TerminalBlock_Phoenix_MKDS-1,5-2_1x02_P5.00mm_Horizontal
Switch: Master Switch; TerminalBlock_Phoenix_MKDS-1,5-2_1x02_P5.00mm_Horizontal
U1, U2, U4, U6, U7: XL4015; TO-263-5_TabPin3

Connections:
5V: 5V Out.1, 5V Out.2, 5V Out.3, -> Actuator Card.1, C10.1, C14.1, L1.2, R2.1, R12.1
12V: 12V Out.1, 12V Out.2, 12V Out.3, -> Actuator Card.3, C1.1, C6.1, L2.2, R4.1, R20.1
24V: 24V Out.1, 24V Out.2, C13.1, C17.1, L4.2, R6.1, R14.1
ADJ1: -> Actuator Card.6, C29.1, C32.1, L6.2, R16.1, RV2.2, Servo 2 Out.1, Servo 2 Out.2
GND: 5V.1 (K), 12V.1 (K), 24V.1 (K), -> Actuator Card.4, -> Actuator Card.5, C1.2, C6.2, C10.2, C12.2, C13.2, C14.2, C17.2, C29.2, C31.2, C32.2, C33.2, D2.2 (A), D3.2 (A), D5.2 (A), D7.2 (A), D8.2 (A), GND.1, GND.2, GND.1, GND.2, LIPO 1.N (NEG), Lipo Voltage.2, R3.2, R7.2, R9.2, R10.2, R21.2, RV2.3, RV3.3, Servo1.1 (K), Servo2.1 (K), U1.1 (GND), U2.1 (GND), U4.1 (GND), U6.1 (GND), U7.1 (GND)
unnamed: D2.1 (K), L2.1, U1.3 (SW)
unnamed: D3.1 (K), L1.1, U2.3 (SW)
unnamed: 12V.2 (A), R4.2
unnamed: D5.1 (K), L4.1, U4.3 (SW)
unnamed: D7.1 (K), L6.1, U6.3 (SW)
unnamed: D8.1 (K), L7.1, U7.3 (SW)
unnamed: 5V.2 (A), R12.2
unnamed: 24V.2 (A), R14.2
unnamed: R15.2, Servo1.2 (A)
unnamed: R16.2, Servo2.2 (A)
unnamed: LIPO 1.P (POS), LIPO 2.N (NEG)
unnamed: Emergency.1, LIPO 2.P (POS), Lipo Voltage.1
unnamed: Emergency.2, Switch.1
unnamed: R20.2, R21.1, U1.2 (FB)
unnamed: C4.2, U1.4 (VC)
unnamed: R2.2, R3.1, U2.2 (FB)
unnamed: C5.2, U2.4 (VC)
unnamed: R6.2, R7.1, U4.2 (FB)
unnamed: C9.2, U4.4 (VC)
unnamed: R9.1, RV2.1, U6.2 (FB)
unnamed: C25.2, U6.4 (VC)
unnamed: R10.1, RV3.1, U7.2 (FB)
unnamed: C27.2, U7.4 (VC)
SERVO: -> Actuator Card.2, C31.1, C33.1, L7.2, R15.1, RV3.2, Servo 1 Out.1, Servo 1 Out.2
SUPPLY: D6.2 (A), Switch.2
VDC: C4.1, C5.1, C9.1, C12.1, C25.1, C27.1, D6.1 (K), U1.5 (VIN), U2.5 (VIN), U4.5 (VIN), U6.5 (VIN), U7.5 (VIN)
